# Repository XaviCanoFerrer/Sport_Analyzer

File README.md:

# Sport_Analyzer

Sport Analyzer is a battery powered acquisition and visualization device for measuring sport performance and rehabilitation. The device interfaces with an incremental encoder and a load cell enabling sport scientists and coaches and rehabilitators to collect and visualize the data without the need of a computer or software interaction.

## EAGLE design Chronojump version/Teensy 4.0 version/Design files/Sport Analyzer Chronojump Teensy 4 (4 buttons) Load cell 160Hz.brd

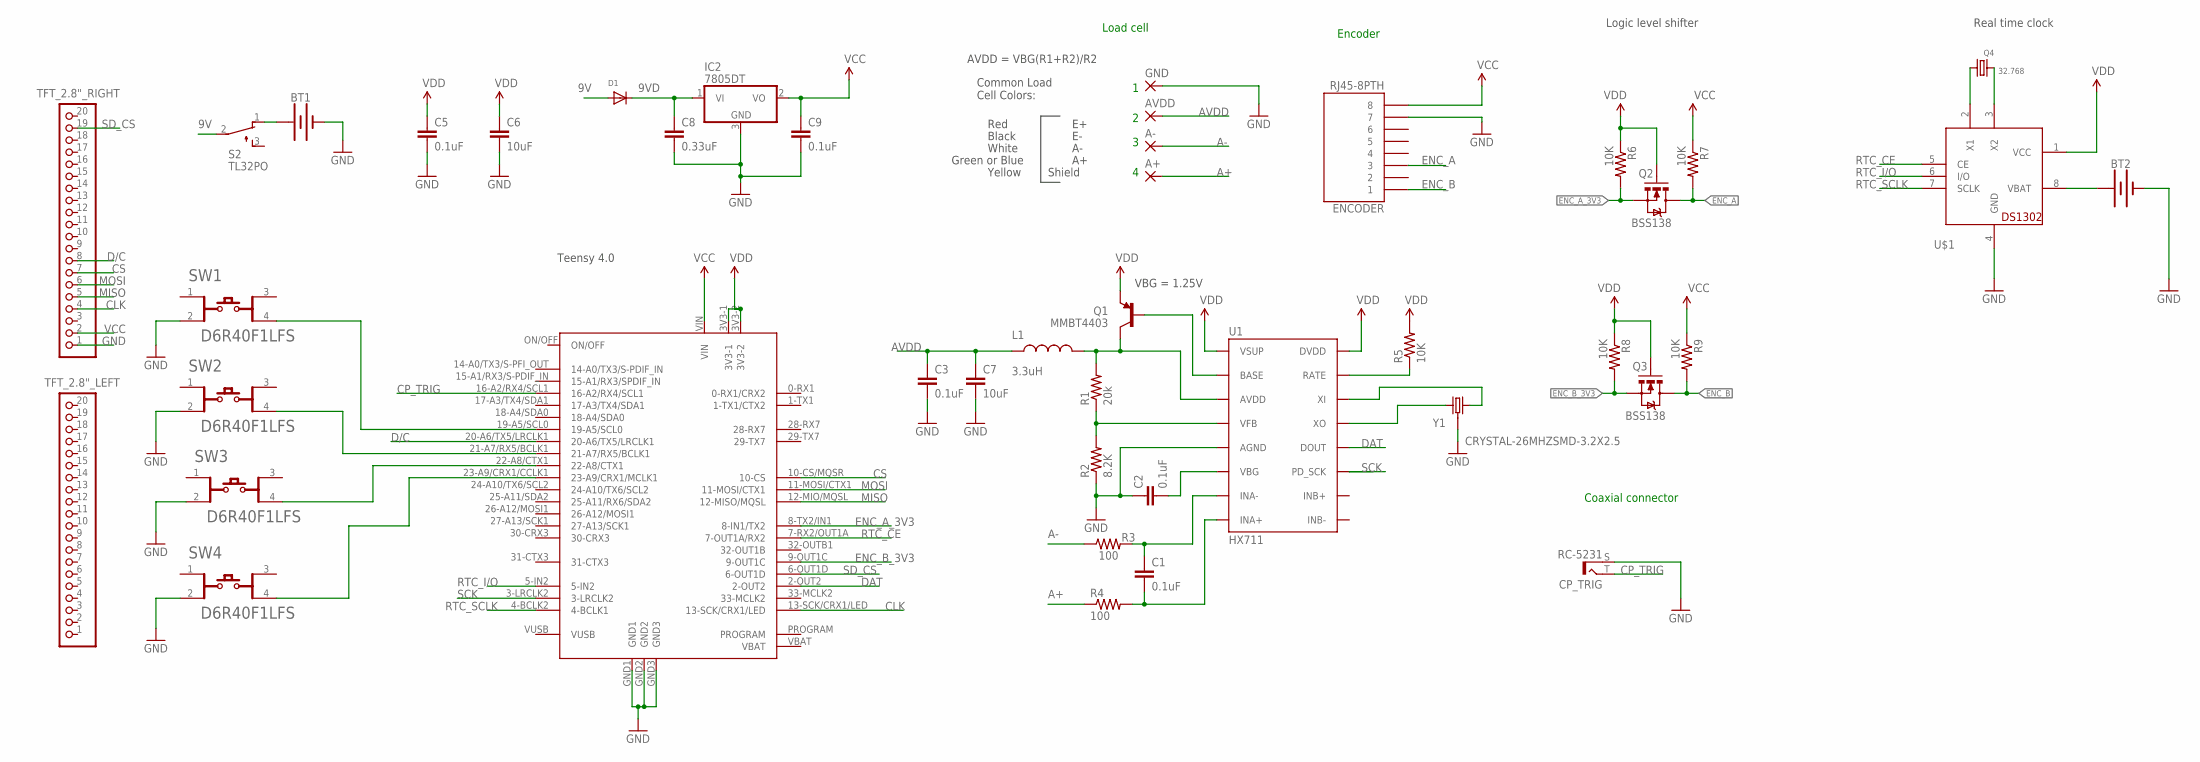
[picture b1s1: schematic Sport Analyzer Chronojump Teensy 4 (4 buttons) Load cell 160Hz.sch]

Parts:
A+: 3,81/1,4
A-: 3,81/1,4
AVDD: 3,81/1,4
BT1: BATTERY-9V; BATTCON_9V
BT2: BATTERY-12MM_SMD; BATTCON_12MM
C1, C2, C3, C5, C9: 0.1uF; 0603-CAP
C6, C7: 10uF; 1210
C8: 0.33uF; 0603-CAP
CP_TRIG: RC-5231
D1: DIODESOD-123; SOD-123
ENCODER: RJ45-8PTH; RJ45-8
GND: 3,81/1,4
IC2: 7805DT; TO252
L1: 3.3uH; 0805
Q1: MMBT4403; SOT23-3
Q2, Q3: BSS138; SOT23-3
Q4: 32.768; CRYSTAL_8X3.8
R1: 20k; 0603-RES
R2: 8.2K; 0603-RES
R3, R4: 100; 0603-RES
R5, R6, R7, R8, R9: 10K; 0603-RES
S2: TL32PO; TL3XPO
SW1, SW2, SW3, SW4: C&K_COMPONENTS_D6R40F1LFSC&K_COMPONENTS_D6R40F1LF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; C&K_COMPONENTS_D6R40F1LFS_0
TFT_2.8"_LEFT, TFT_2.8"_RIGHT: PINHD-1X20; 1X20
U1: HX711; SO16
U$1: DS1302; DIL08-ROUND
U$2: TEENSY40
Y1: CRYSTAL-26MHZSMD-3.2X2.5; CRYSTAL-SMD-3.2X2.5MM

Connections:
9V: D1.A, S2.2
9VD: C8.1, D1.C, IC2.1 (VI)
A+: A+.1, R4.1
A-: A-.1, R3.1
AVDD: AVDD.1, C3.1, C7.1, L1.1
CLK: TFT_2.8"_RIGHT.4, U$2.13-SCK/CRX1/LED
CP_TRIG: CP_TRIG.T, U$2.16-A2/RX4/SCL1
CS: TFT_2.8"_RIGHT.7, U$2.10-CS/MQSR (10-CS)
D/C: TFT_2.8"_RIGHT.8, U$2.20-A6/TX5/LRCLK1
DAT: U1.12 (DOUT), U$2.2-OUT2
ENC_A: ENCODER.3, Q2.3 (D), R7.2
ENC_A_3V3: Q2.2 (S), R6.2, U$2.8-TX2/IN1 (8-IN1/TX2)
ENC_B: ENCODER.1, Q3.3 (D), R9.2
ENC_B_3V3: Q3.2 (S), R8.2, U$2.9-OUT1C
GND: BT1.-, BT2.GND (-), C2.1, C3.2, C5.2, C6.2, C7.2, C8.2, C9.2, CP_TRIG.S, ENCODER.7, GND.1, IC2.3 (GND), R2.1, SW1.2, SW2.2, SW3.2, SW4.2, TFT_2.8"_RIGHT.1, U1.5 (AGND), U$1.4 (GND), U$2.GND1, U$2.GND2, U$2.GND3, Y1.2 (GND), Y1.4 (GND)
MISO: TFT_2.8"_RIGHT.5, U$2.12-MIO/MQSL (12-MISO/MQSL)
MOSI: TFT_2.8"_RIGHT.6, U$2.11-MOSI/CTX1
unnamed: R5.1, U1.15 (RATE)
unnamed: C1.1, R3.2, U1.7 (INA-)
unnamed: C1.2, R4.2, U1.8 (INA+)
unnamed: Q1.1 (B), U1.2 (BASE)
unnamed: L1.2, Q1.3 (C), R1.2, U1.3 (AVDD)
unnamed: R1.1, R2.2, U1.4 (VFB)
unnamed: C2.2, U1.6 (VBG)
unnamed: Q4.P$4 (2), U$1.2 (X1)
unnamed: Q4.P$1 (1), U$1.3 (X2)
unnamed: SW1.4, U$2.19-A5/SCL0
unnamed: SW2.4, U$2.21-A7/RX5/BCLK1
unnamed: SW3.4, U$2.22-A8/CTX1
unnamed: SW4.4, U$2.23-A9/CRX1/CCLK1 (23-A9/CRX1/MCLK1)
unnamed: U1.13 (XO), Y1.1
unnamed: U1.14 (XI), Y1.3 (2)
unnamed: BT2.PWR@1 (+), U$1.8 (VBAT)
unnamed: BT1.+, S2.1 (O)
RTC_CE: U$1.5 (CE), U$2.7-RX2/OUT1A (7-OUT1A/RX2)
RTC_I/O: U$1.6 (I/O), U$2.5-IN2
RTC_SCLK: U$1.7 (SCLK), U$2.4-BCLK2 (4-BCLK1)
SCK: U1.11 (PD_SCK), U$2.3-LRCLK2
SD_CS: TFT_2.8"_RIGHT.19, U$2.6-OUT1D
VCC: C9.1, ENCODER.8, IC2.2 (VO), R7.1, R9.1, TFT_2.8"_RIGHT.2, U$2.VIN
VDD: C5.1, C6.1, Q1.2 (E), Q2.1 (G), Q3.1 (G), R5.2, R6.1, R8.1, U1.1 (VSUP), U1.16 (DVDD), U$1.1 (VCC), U$2.3V3-1, U$2.3V3-2

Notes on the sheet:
VBG = 1.25V
AVDD = VBG(R1+R2)/R2
Red
Black
White
Green or Blue
Common Load Cell Colors:
Shield
Yellow
Encoder
Coaxial connector
Load cell
Logic level shifter
Teensy 4.0
Real time clock

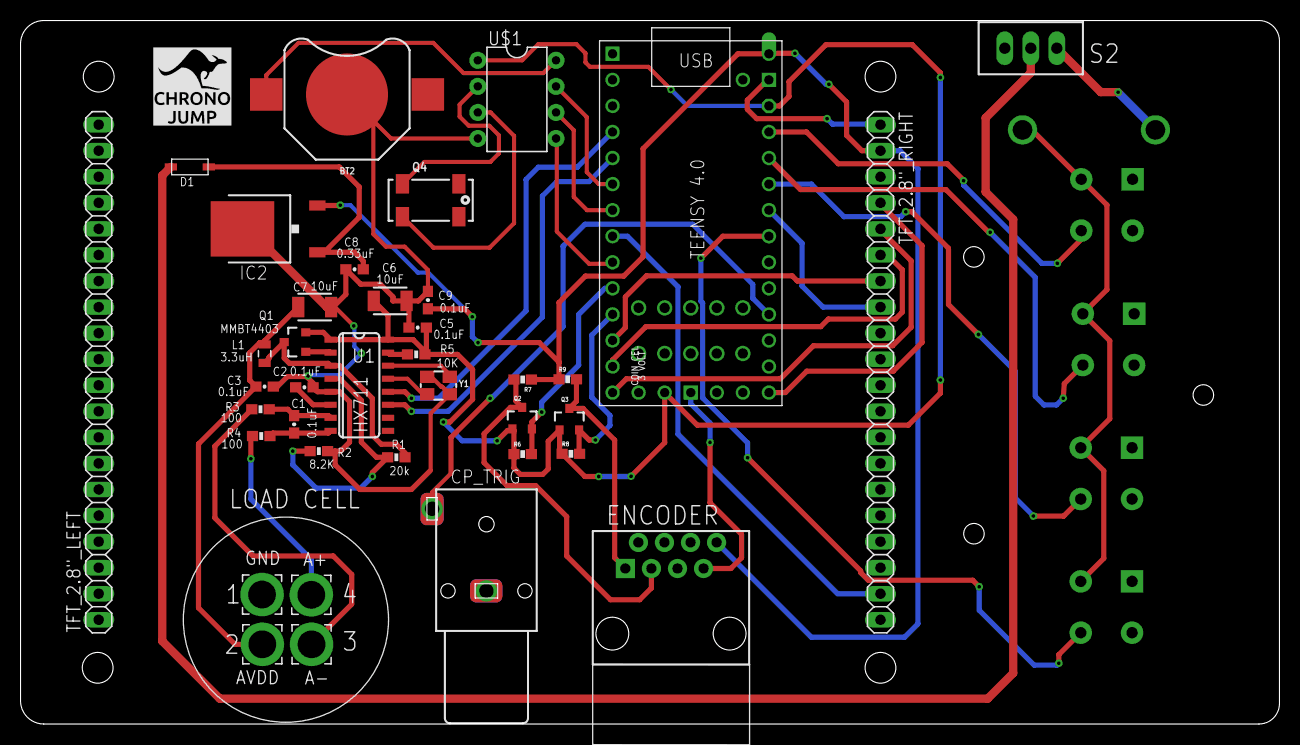
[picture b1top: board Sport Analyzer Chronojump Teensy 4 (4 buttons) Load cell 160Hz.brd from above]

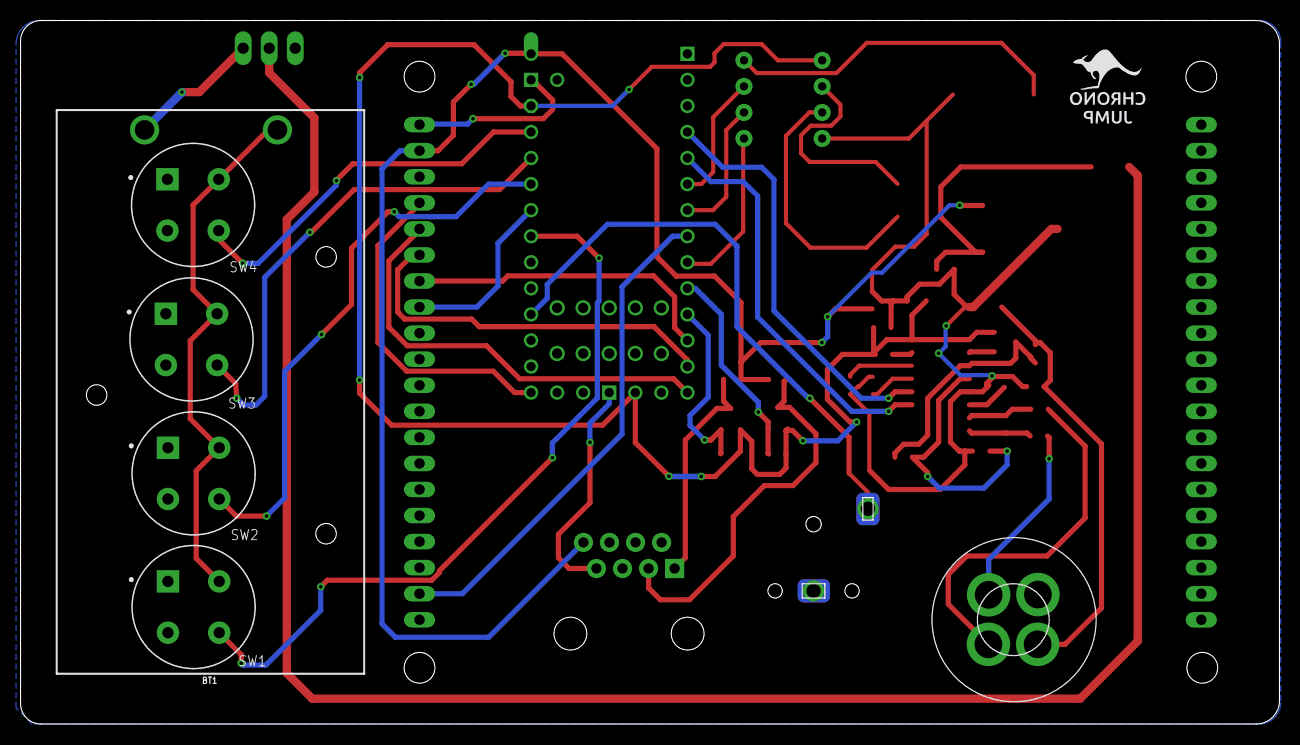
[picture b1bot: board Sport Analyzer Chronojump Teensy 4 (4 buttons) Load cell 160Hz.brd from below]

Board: 2 copper layers, 122.7 x 68.6 mm, 43 parts (5 on the bottom side), 41 nets.

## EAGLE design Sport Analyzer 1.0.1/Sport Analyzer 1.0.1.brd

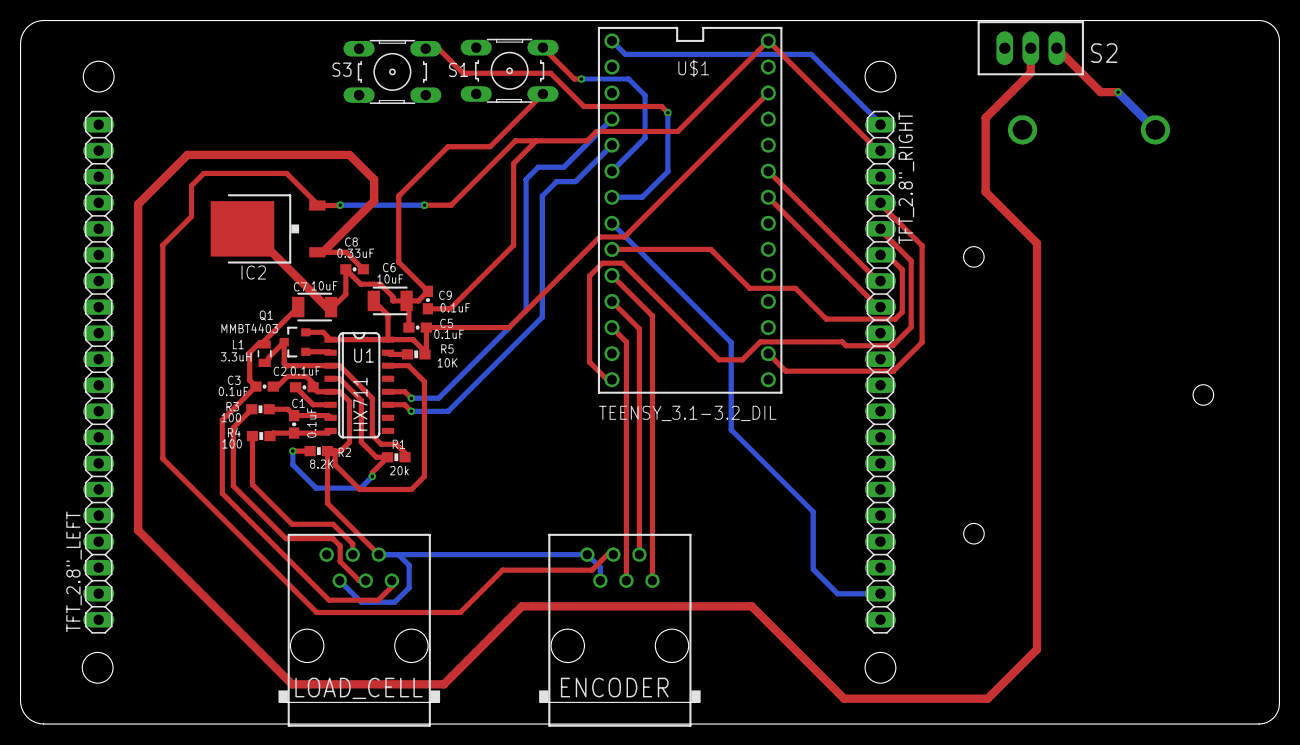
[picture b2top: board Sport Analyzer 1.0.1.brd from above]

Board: 2 copper layers, 122.7 x 68.6 mm, 26 parts (1 on the bottom side), 28 nets.

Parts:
BT1: BATTCON_9V
C1, C2, C3, C5, C9: 0.1uF; 0603-CAP
C6, C7: 10uF; 1210
C8: 0.33uF; 0603-CAP
ENCODER: RJ11-2L-B; RJ11-NO_SHIELD
IC2: 7805DT; TO252
L1: 3.3uH; 0805
LOAD_CELL: RJ11-2L-B; RJ11-NO_SHIELD
Q1: MMBT4403; SOT23-3
R1: 20k; 0603-RES
R2: 8.2K; 0603-RES
R3, R4: 100; 0603-RES
R5: 10K; 0603-RES
S1, S3: B3F-10XX
S2: TL32PO; TL3XPO
TFT_2.8"_LEFT, TFT_2.8"_RIGHT: 1X20
U1: HX711; SO16
U$1: TEENSY_3.1-3.2_DIL; TEENSY_3.0-3.2&LC_DIL

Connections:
9V: C8.1, IC2.1, S2.2
A+: LOAD_CELL.3, R4.1
A-: LOAD_CELL.4, R3.1
AVDD: C3.1, C7.1, L1.1, LOAD_CELL.6
CLK: TFT_2.8"_RIGHT.4, U$1.14/A0
CS: TFT_2.8"_RIGHT.7, U$1.21/A7
D/C: TFT_2.8"_RIGHT.8, U$1.20/A6
DAT: U1.12, U$1.2
ENC_A: ENCODER.6, U$1.8
ENC_B: ENCODER.5, U$1.9
ENC_Z: ENCODER.4, U$1.10
GND: BT1.-, C2.1, C3.2, C5.2, C6.2, C7.2, C8.2, C9.2, ENCODER.1, ENCODER.2, IC2.3, LOAD_CELL.2, LOAD_CELL.5, R2.1, S1.4, S3.4, TFT_2.8"_RIGHT.1, U1.5, U1.14, U$1.GND
MISO: TFT_2.8"_RIGHT.5, U$1.12
MOSI: TFT_2.8"_RIGHT.6, U$1.7
unnamed: R5.1, U1.15
unnamed: C1.1, R3.2, U1.7
unnamed: C1.2, R4.2, U1.8
unnamed: Q1.1, U1.2
unnamed: L1.2, Q1.3, R1.2, U1.3
unnamed: R1.1, R2.2, U1.4
unnamed: C2.2, U1.6
unnamed: S1.2, U$1.4
unnamed: S3.2, U$1.5
unnamed: BT1.+, S2.1
SCK: U1.11, U$1.3
SD_CS: TFT_2.8"_RIGHT.19, U$1.6
VCC: C9.1, ENCODER.3, IC2.2, TFT_2.8"_RIGHT.2, U$1.VIN
VDD: C5.1, C6.1, Q1.2, R5.2, U1.1, U1.16, U$1.3.3V

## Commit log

2021-06-15 BOM Magnets Update
2021-06-21 3rd commit
2021-06-28 SA 1.0.1
2021-07-02 SP 1.0.1 PMMA case 1
2021-07-02 SA 1.0.1 Component names
2021-07-03 Conical pulley data
2021-07-04 Prism files 1
2021-07-10 SA 1.0.1 (4)
2021-07-14 Presentation update
2021-07-14 Data update
2021-07-16 Isometric data
2021-07-19 Shoulder MVC data 2
2021-07-28 Calibration correction
2021-07-30 More data figures
2021-08-01 Documentation 1.0.1
2021-08-05 Update Load cell calibration eq
2021-08-07 SD long recording fix
2021-08-07 Inventor design files
2021-09-09 Pictures update
2021-09-30 Bosco 60s test data 1
2021-10-01 pulses/mm correction
2021-10-01 Bosco test py
2021-10-15 Assembly instructions
2021-10-15 Assembly instructions PDF
2021-10-15 Removed old folder
2021-10-21 Assembly instructions Figures 8-9
2021-11-05 Article
2021-11-18 Article writing 1
2021-11-24 Article Conclusions 1
2021-11-25 Data update 2
2022-02-17 Conical data
2022-03-05 TFT soldering
2022-03-05 Battery holder
2022-03-10 Teensy 4 version
2022-04-05 Teensy 4 logic level shifters V2
2022-05-04 Teensy 4 update
2022-05-18 Chronojump case
2022-06-02 Teensy 4 CJ firmware
2022-06-08 Chronojump version RTC/4buttons
2022-06-10 RTC DS1302 v1
2022-10-26 Load cell 160 Hz

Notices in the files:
parts and their libraries:
SparkFun-Capacitors: Licensing: Creative Commons ShareAlike 4.0 International - https://creativecommons.org/licenses/by-sa/4.0
microbuilder: This work is placed in the public domain, and may be freely used for commercial and non-commercial work with the following conditions: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
